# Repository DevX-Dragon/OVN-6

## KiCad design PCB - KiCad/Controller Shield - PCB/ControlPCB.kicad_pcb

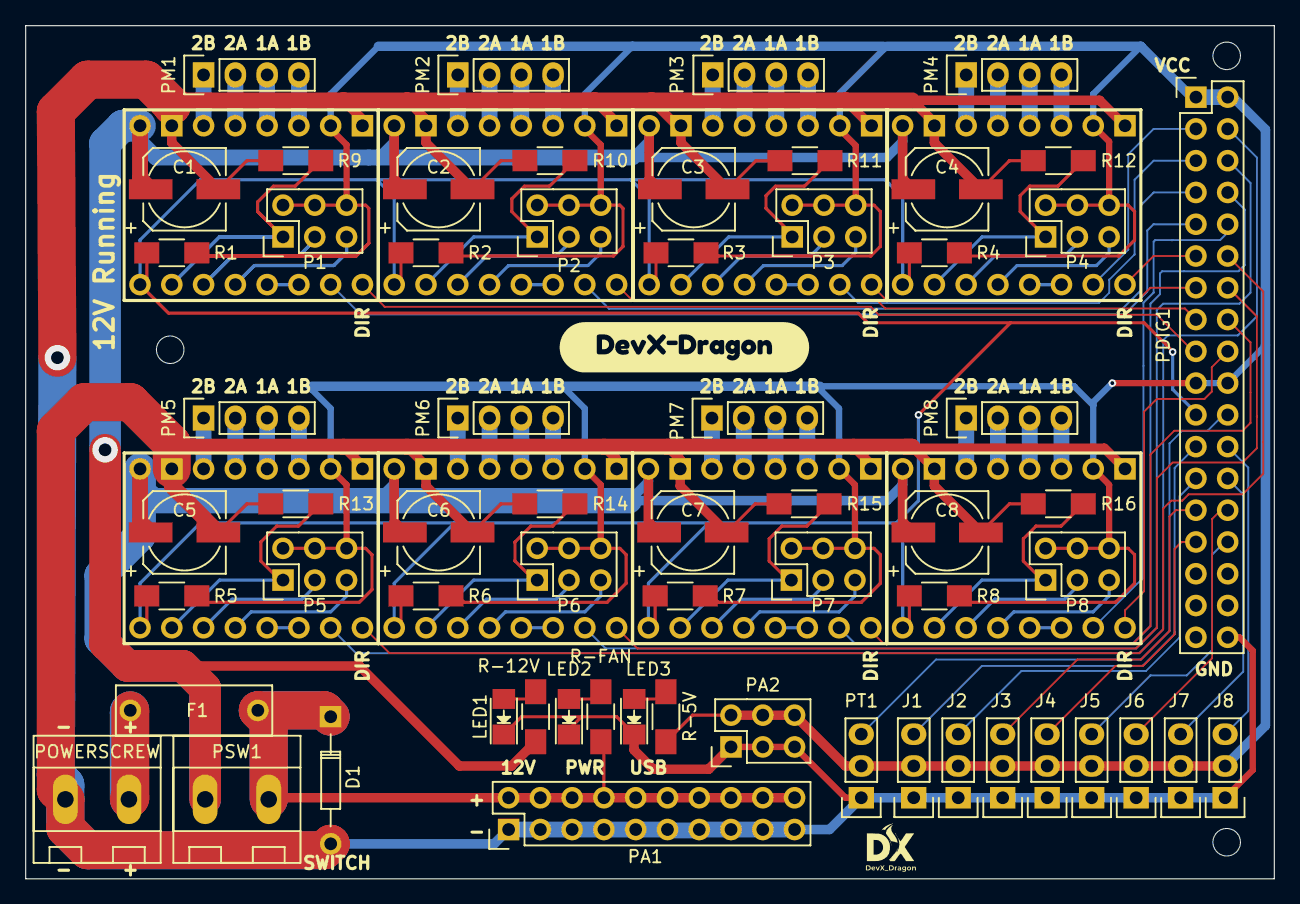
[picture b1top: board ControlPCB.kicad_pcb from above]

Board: 2 copper layers, 99.8 x 68.2 mm, 71 parts (0 on the bottom side), 98 nets.

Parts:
C1, C2, C3, C4, C5, C6, C7, C8: CP1_Small; c_elec_6.3x5.7
D1: D_Small; Diode_DO-35_SOD27_Horizontal_RM10
F1: F_Small; Fuse_TE5_Littlefuse-395Series
J1: O1; Pin_Header_Straight_1x03
J2: O2; Pin_Header_Straight_1x03
J3: O3; Pin_Header_Straight_1x03
J4: O4; Pin_Header_Straight_1x03
J5: O5; Pin_Header_Straight_1x03
J6: O6; Pin_Header_Straight_1x03
J7: O7; Pin_Header_Straight_1x03
J8: O8; Pin_Header_Straight_1x03
LED1: 12V-LED; LED_1206
LED2: FAN-LED; LED_1206
LED3: 5V-LED; LED_1206
P1, P2, P3, P4, P5, P6, P7, P8: CONN_02X03; Pin_Header_Straight_2x03
PA1: AUX12V; Pin_Header_Straight_2x10
PA2: AUX5V; Pin_Header_Straight_2x03
PDIG1: Conn_02x18_Odd_Even; Pin_Header_Straight_2x18
PM1, PM2, PM3, PM4, PM5, PM6, PM7, PM8: CONN_01X04; Pin_Header_Straight_1x04
POWERSCREW: Screw_Terminal_01x02; Conn2
PSW1: Screw_Terminal_01x02; Conn2
PT1: TL; Pin_Header_Straight_1x03
R1, R2, R3, R4, R5, R6, R7, R8, R9, R10, R11, R12, R13, R14, R15, R16: R; R_1206_HandSoldering
R-5V: 220; R_1206_HandSoldering
R-12V: 560; R_1206_HandSoldering
R-FAN: 560; R_1206_HandSoldering
U1, U2, U3, U4, U5, U6, U7, U8: POLOLU_A4988; SWDIP8_.6W
kibuzzard-699841ED: G***; kibuzzard-699841ED

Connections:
1AM1: PM1.3, U1.4
1AM2: PM2.3, U2.4
1AM3: PM3.3, U3.4
1AM4: PM4.3, U4.4
1AM5: PM5.3, U5.4
1AM6: PM6.3, U6.4
1AM7: PM7.3, U7.4
1AM8: PM8.3, U8.4
1BM1: PM1.4, U1.3
1BM2: PM2.4, U2.3
1BM3: PM3.4, U3.3
1BM4: PM4.4, U4.3
1BM5: PM5.4, U5.3
1BM6: PM6.4, U6.3
1BM7: PM7.4, U7.3
1BM8: PM8.4, U8.3
2AM1: PM1.2, U1.5
2AM2: PM2.2, U2.5
2AM3: PM3.2, U3.5
2AM4: PM4.2, U4.5
2AM5: PM5.2, U5.5
2AM6: PM6.2, U6.5
2AM7: PM7.2, U7.5
2AM8: PM8.2, U8.5
2BM1: PM1.1, U1.6
2BM2: PM2.1, U2.6
2BM3: PM3.1, U3.6
2BM4: PM4.1, U4.6
2BM5: PM5.1, U5.6
2BM6: PM6.1, U6.6
2BM7: PM7.1, U7.6
2BM8: PM8.1, U8.6
+12V: C1.1, C2.1, C3.1, C4.1, C5.1, C6.1, C7.1, C8.1, PSW1.2, R-12V.2, U1.8, U2.8, U3.8, U4.8, U5.8, U6.8, U7.8, U8.8
DIRM1: PDIG1.17, U1.16
DIRM2: PDIG1.15, U2.16
DIRM3: PDIG1.13, U3.16
DIRM4: PDIG1.11, U4.16
DIRM5: PDIG1.12, U5.16
DIRM6: PDIG1.14, U6.16
DIRM7: PDIG1.16, U7.16
DIRM8: PDIG1.18, U8.16
ENABLEM: PDIG1.21, R1.1, R2.1, R3.1, R4.1, R5.1, R6.1, R7.1, R8.1, U1.9, U2.9, U3.9, U4.9, U5.9, U6.9, U7.9, U8.9
GND: C1.2, C2.2, C3.2, C4.2, C5.2, C6.2, C7.2, C8.2, D1.2, J1.1, J2.1, J3.1, J4.1, J5.1, J6.1, J7.1, J8.1, LED1.1, LED2.1, LED3.1, PA1.1, PA1.3, PA1.5, PA1.7, PA1.9, PA1.11, PA1.13, PA1.15, PA1.17, PA1.19, PA2.1, PA2.3, PA2.5, PDIG1.36, POWERSCREW.1, PT1.1, R9.2, R10.2, R11.2, R12.2, R13.2, R14.2, R15.2, R16.2, U1.1, U1.7, U2.1, U2.7, U3.1, U3.7, U4.1, U4.7, U5.1, U5.7, U6.1, U6.7, U7.1, U7.7, U8.1, U8.7
unnamed: LED2.2, R-FAN.1
unnamed: LED1.2, R-12V.1
unnamed: LED3.2, R-5V.1
unnamed: F1.2, POWERSCREW.2
unnamed: P1.1, U1.12
unnamed: P1.3, U1.11
unnamed: P1.5, R9.1, U1.10
unnamed: P2.1, U2.12
unnamed: P2.3, U2.11
unnamed: P2.5, R10.1, U2.10
unnamed: P3.1, U3.12
unnamed: P3.3, U3.11
unnamed: P3.5, R11.1, U3.10
unnamed: P4.1, U4.12
unnamed: P4.3, U4.11
unnamed: P4.5, R12.1, U4.10
unnamed: P5.1, U5.12
unnamed: P5.3, U5.11
unnamed: P5.5, R13.1, U5.10
unnamed: P6.1, U6.12
unnamed: P6.3, U6.11
unnamed: P6.5, R14.1, U6.10
unnamed: P7.1, U7.12
unnamed: P7.3, U7.11
unnamed: P7.5, R15.1, U7.10
unnamed: P8.1, U8.12
unnamed: P8.3, U8.11
unnamed: P8.5, R16.1, U8.10
unnamed: U1.13, U1.14
unnamed: U2.13, U2.14
unnamed: U3.13, U3.14
unnamed: U4.13, U4.14
unnamed: U5.13, U5.14
unnamed: U6.13, U6.14
unnamed: U7.13, U7.14
unnamed: U8.13, U8.14
SOPTO1: J1.3, PDIG1.23
SOPTO2: J2.3, PDIG1.25
SOPTO3: J3.3, PDIG1.27
SOPTO4: J4.3, PDIG1.29
SOPTO5: J5.3, PDIG1.30
SOPTO6: J6.3, PDIG1.28
SOPTO7: J7.3, PDIG1.26
SOPTO8: J8.3, PDIG1.24
STEPM1: PDIG1.9, U1.15
STEPM2: PDIG1.7, U2.15
STEPM3: PDIG1.5, U3.15
STEPM4: PDIG1.3, U4.15
STEPM5: PDIG1.4, U5.15
STEPM6: PDIG1.6, U6.15
STEPM7: PDIG1.8, U7.15
STEPM8: PDIG1.10, U8.15
STOOL: PDIG1.22, PT1.3
VCC: J1.2, J2.2, J3.2, J4.2, J5.2, J6.2, J7.2, J8.2, P1.2, P1.4, P1.6, P2.2, P2.4, P2.6, P3.2, P3.4, P3.6, P4.2, P4.4, P4.6, P5.2, P5.4, P5.6, P6.2, P6.4, P6.6, P7.2, P7.4, P7.6, P8.2, P8.4, P8.6, PA2.2, PA2.4, PA2.6, PDIG1.1, PDIG1.2, PDIG1.19, PDIG1.20, PT1.2, R1.2, R2.2, R3.2, R4.2, R5.2, R6.2, R7.2, R8.2, R-5V.2, U1.2, U2.2, U3.2, U4.2, U5.2, U6.2, U7.2, U8.2
VDD: D1.1, F1.1, PA1.2, PA1.4, PA1.6, PA1.8, PA1.10, PA1.12, PA1.14, PA1.16, PA1.18, PA1.20, PSW1.1, R-FAN.2

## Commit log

2026-02-23 bye bye
2026-02-23 Initial Upload of KiCad Files
2026-02-25 Initial 3D Files Upload + Art 5&6 and Gripper STLs and .blend only
2026-02-26 Art 3&4 STL upload | need to fix the body holes
